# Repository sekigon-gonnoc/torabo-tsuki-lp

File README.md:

# torabo-tsuki LP

torabo-tsuki LP（トラボ付きLP）はトラックボール付きの無線分割キーボードキットです。

トラックボール(25 or 19mm)の高さを低く抑えることで、キーを打つときや持ち運びの邪魔になりにくくなっています。
無線接続に適したハードウェア・ソフトウェア構成により低消費電力を実現しており、連続して数か月間使用可能です。バッテリーは乾電池なので、残量や安全性を気にしながら定期的に充電する必要がありません。

[BOOTH](https://nogikes.booth.pm/items/7200248)にて販売中です。

**MX版の情報は[こちら](https://github.com/sekigon-gonnoc/torabo-tsuki)**

|||
|-|-|
|Sサイズ, 右25mmボール|Sサイズ, 右25mmボール|
|||
|Sサイズ, 右19mmボール|Sサイズ, 右19mmボール|

## [ビルドガイド](build-guide.md)

## 特徴

* 主要部品実装済み
  * ソケットやダイオードなどの部品は実装済みです。半田付けが必要な部品は電池ボックスだけです。
* 乾電池各1本で長期間動作
  * Ni-MH電池またはアルカリ電池で動作します。
  * 無線での使用にあわせて調整されたハードウェア・ソフトウェア構成により、乾電池でも数か月間利用できます。
* トラックボールの設置位置が調整可能
  * トラックボールを取り付ける位置を調整して、自分にとって一番操作しやすい位置に設置できます。ボールの高さを抑えたことでキーを打つときの邪魔になりにくなっています。
  * 左トラックボール、デュアルトラックボールにすることもできます。
  * トラックボールのサイズは25mmまたは19mmから選択できます。
* ZMK対応
  * keymap-editorやZMK Studioを使用して簡単にキーマップが変更できます。

## 使用上の注意

* 異臭や煙が出たときは、ただちに使用を中止して電源を切り電池を抜いてください。
* 電池から漏れた液が目に入った場合は、失明する恐れがあるのですぐにきれいな水でよく洗い、医師の診断を受けてください。
* 電池の+-を正しくセットしてください。
* 使い切った電池は速やかに取り出してください。
* 長期間使用しない場合は電池を取り出してください。

## 設計データについて

本リポジトリで基板・トラックボールケース・電池カバーの設計データを公開しています。

ライセンスにしたがって自由に利用していただいて構いませんが、問い合わせには対応しません。

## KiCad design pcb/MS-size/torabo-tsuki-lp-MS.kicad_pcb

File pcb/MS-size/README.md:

\# torabo-tsuki LP(MS)

Mサイズの17mmピッチ版です。

動作未確認

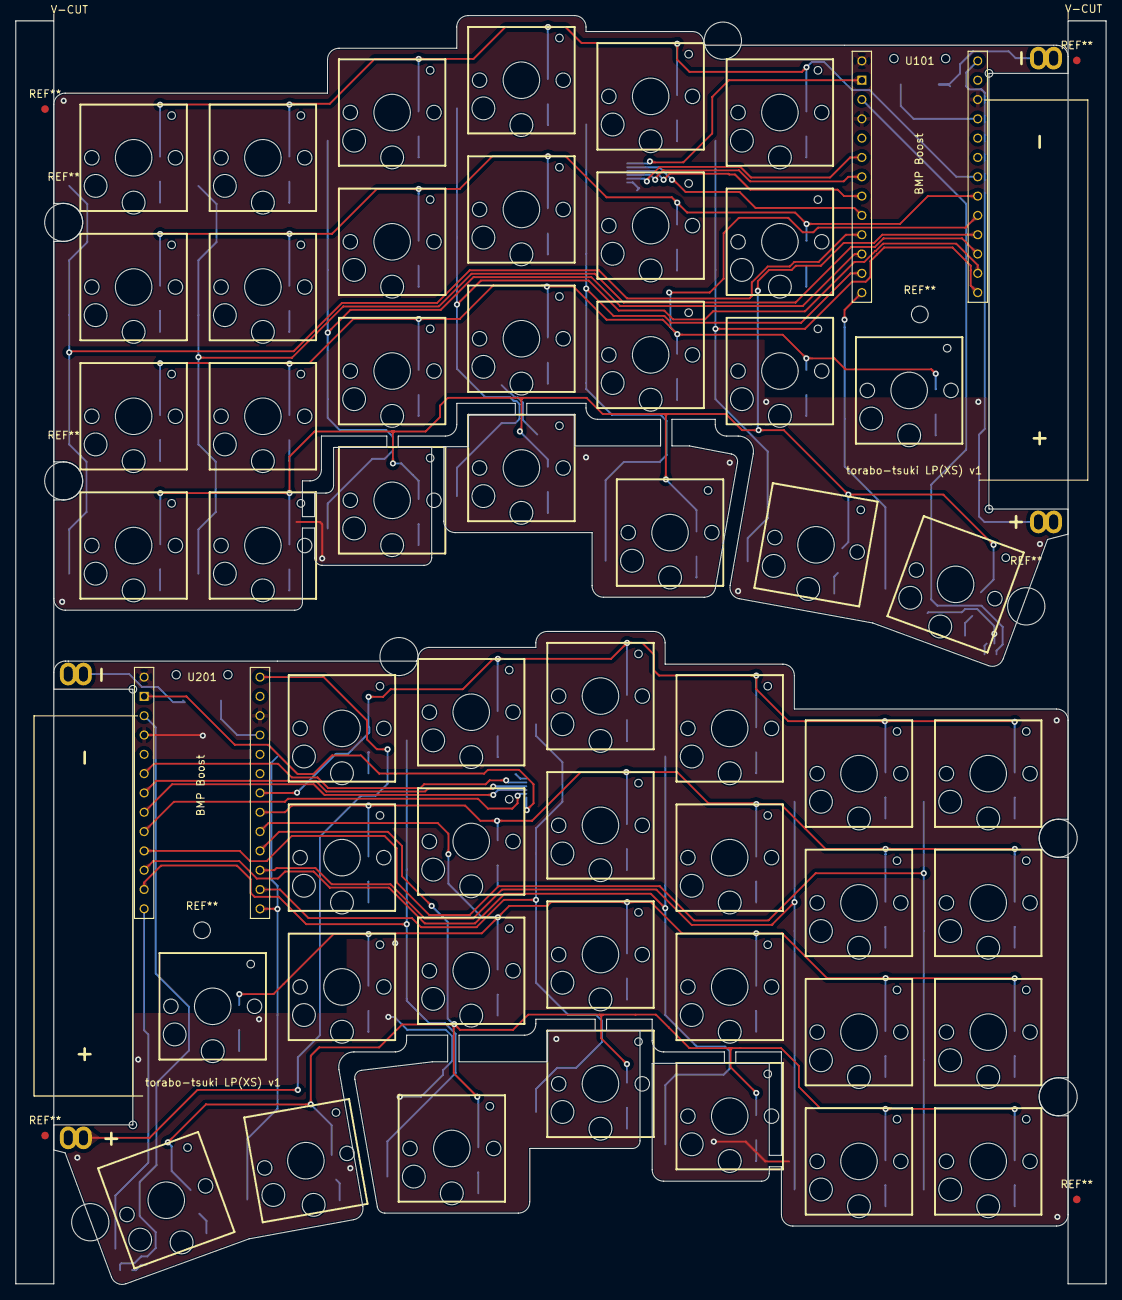
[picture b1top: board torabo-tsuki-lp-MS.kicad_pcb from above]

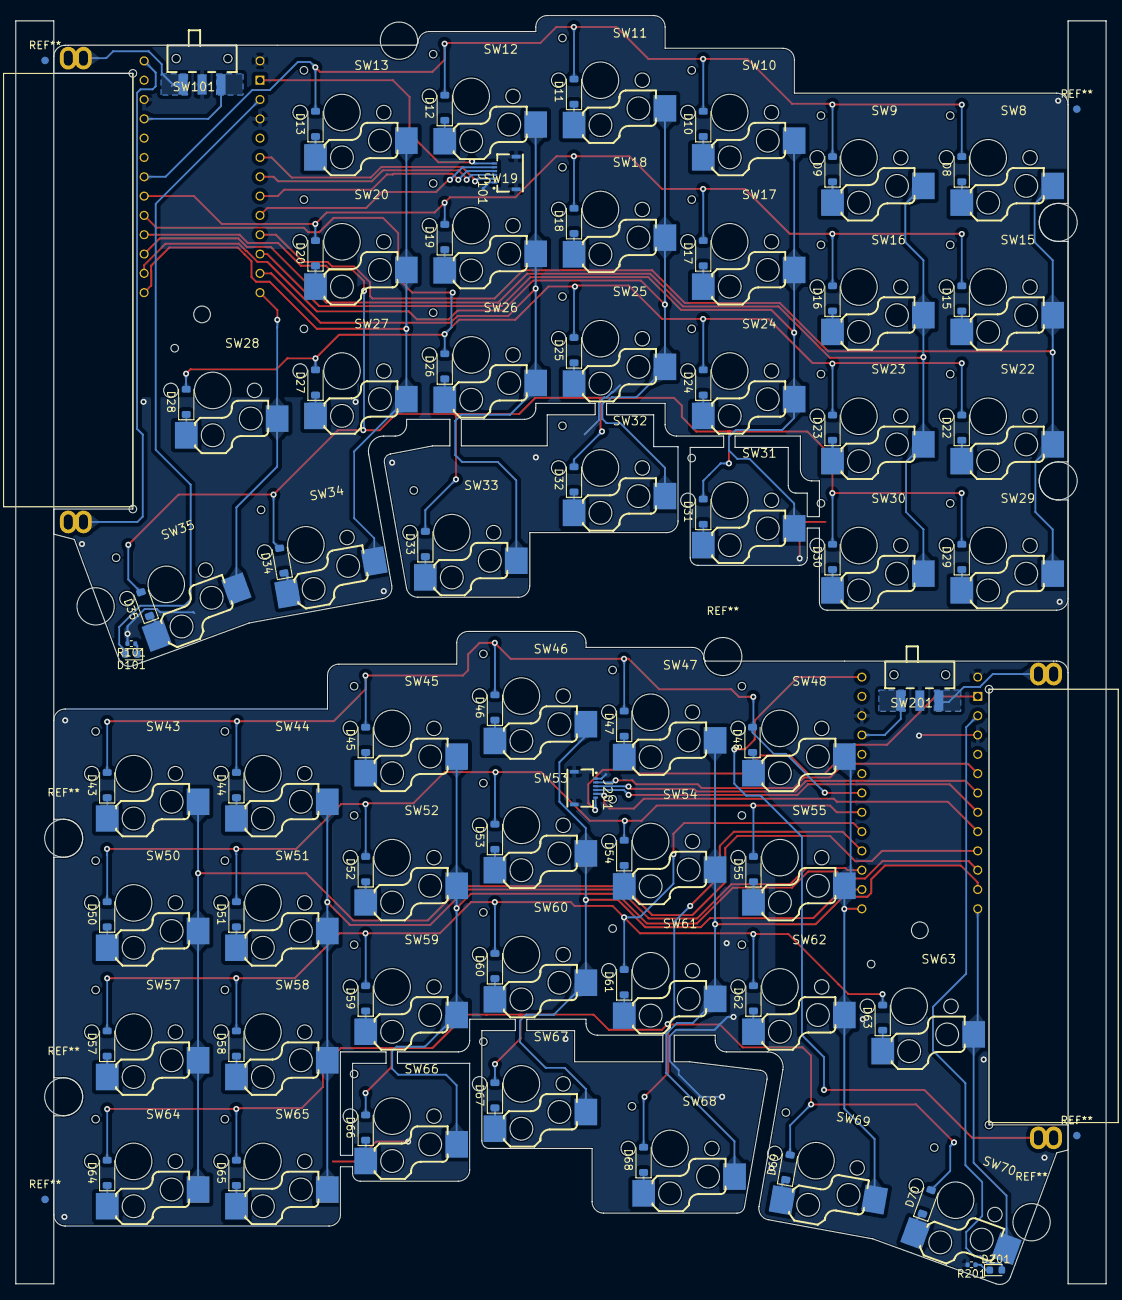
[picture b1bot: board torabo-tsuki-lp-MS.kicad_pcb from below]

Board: 2 copper layers, 143.4 x 166.8 mm, 118 parts (114 on the bottom side), 93 nets.

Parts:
BT101, BT201: Battery_Cell; battery_holder
BT102, BT202: Battery_Cell; AAA_Battery_DIP
D8, D9, D10, D11, D12, D13, D15, D16, D17, D18, D19, D20, D22, D23, D24, D25, D26, D27, D28, D29, D30, D31, D32, D33, D34, D35, D43, D44, D45, D46, D47, D48, D50, D51, D52, D53, D54, D55, D57, D58, D59, D60, D61, D62, D63, D64, D65, D66, D67, D68, D69, D70: D_Small; D_SOD-123
D101, D201: LED_Small; LED_0603_1608Metric
J101, J201: Conn_01x06_MountingPin; GT-F0501SR10-06S1101
R101, R201: 330; R_0402_1005Metric
SW8, SW9, SW10, SW11, SW12, SW13, SW15, SW16, SW17, SW18, SW19, SW20, SW22, SW23, SW24, SW25, SW26, SW27, SW28, SW29, SW30, SW31, SW32, SW33, SW34, SW35, SW43, SW44, SW45, SW46, SW47, SW48, SW50, SW51, SW52, SW53, SW54, SW55, SW57, SW58, SW59, SW60, SW61, SW62, SW63, SW64, SW65, SW66, SW67, SW68, SW69, SW70: SW_Push; CHOC_V2_SOCKET_HANDSOLDERING
SW101, SW201: SW_SPDT; SW-SMD_K3-1280S-F1
U101, U201: BLEMicroPro

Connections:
+BATT: BT101.1 (+), BT102.1 (+), BT201.1 (+), BT202.1 (+), U101.26 (BAT), U201.26 (BAT)
/left/BOOT: SW101.3 (C), U101.23 (BOOT)
/left/COL0: SW8.1, SW15.1, SW22.1, SW29.1, U101.10 (22)
/left/COL1: SW9.1, SW16.1, SW23.1, SW30.1, U101.16 (47)
/left/COL2: SW10.1, SW17.1, SW24.1, SW31.1, U101.11 (23)
/left/COL3: SW11.1, SW18.1, SW25.1, SW32.1, U101.15 (10)
/left/COL4: SW12.1, SW19.1, SW26.1, SW33.1, U101.12 (32)
/left/COL5: SW13.1, SW20.1, SW27.1, SW34.1, U101.14 (9)
/left/COL6: SW28.1, SW35.1, U101.13 (35)
/left/CS: J101.5, U101.9 (20)
/left/LED: D101.2 (A), U101.3 (11)
/left/MOTION: J101.4, U101.8 (19)
/left/ROW1: D8.2 (A), D9.2 (A), D10.2 (A), D11.2 (A), D12.2 (A), D13.2 (A), U101.20 (0)
/left/ROW2: D15.2 (A), D16.2 (A), D17.2 (A), D18.2 (A), D19.2 (A), D20.2 (A), U101.19 (30)
/left/ROW3: D22.2 (A), D23.2 (A), D24.2 (A), D25.2 (A), D26.2 (A), D27.2 (A), D28.2 (A), U101.18 (3)
/left/ROW4: D29.2 (A), D30.2 (A), D31.2 (A), D32.2 (A), D33.2 (A), D34.2 (A), D35.2 (A), U101.17 (46)
/left/SCLK: J101.2, U101.6 (18)
/left/SDIO: J101.3, U101.7 (16)
/right/BOOT: SW201.1 (A), U201.23 (BOOT)
/right/COL0: SW43.1, SW50.1, SW57.1, SW64.1, U201.10 (22)
/right/COL1: SW44.1, SW51.1, SW58.1, SW65.1, U201.16 (47)
/right/COL2: SW45.1, SW52.1, SW59.1, SW66.1, U201.11 (23)
/right/COL3: SW46.1, SW53.1, SW60.1, SW67.1, U201.15 (10)
/right/COL4: SW47.1, SW54.1, SW61.1, SW68.1, U201.12 (32)
/right/COL5: SW48.1, SW55.1, SW62.1, SW69.1, U201.14 (9)
/right/COL6: SW63.1, SW70.1, U201.13 (35)
/right/CS: J201.5, U201.9 (20)
/right/LED: D201.2 (A), U201.3 (11)
/right/MOTION: J201.4, U201.8 (19)
/right/ROW1: D43.2 (A), D44.2 (A), D45.2 (A), D46.2 (A), D47.2 (A), D48.2 (A), U201.20 (0)
/right/ROW2: D50.2 (A), D51.2 (A), D52.2 (A), D53.2 (A), D54.2 (A), D55.2 (A), U201.19 (30)
/right/ROW3: D57.2 (A), D58.2 (A), D59.2 (A), D60.2 (A), D61.2 (A), D62.2 (A), D63.2 (A), U201.18 (3)
/right/ROW4: D64.2 (A), D65.2 (A), D66.2 (A), D67.2 (A), D68.2 (A), D69.2 (A), D70.2 (A), U201.17 (46)
/right/SCLK: J201.2, U201.6 (18)
/right/SDIO: J201.3, U201.7 (16)
GND: J101.1, J101.MP (MountPin), J201.1, J201.MP (MountPin), R101.2, R201.2, SW101.2 (B), SW201.2 (B), U101.1 (GND), U101.4 (GND), U101.24 (GND), U201.1 (GND), U201.4 (GND), U201.24 (GND)
unnamed: BT101.2 (-), BT102.2 (-), SW101.1 (A)
unnamed: BT201.2 (-), BT202.2 (-), SW201.3 (C)
unnamed: D8.1 (K), SW8.2
unnamed: D9.1 (K), SW9.2
unnamed: D10.1 (K), SW10.2
unnamed: D11.1 (K), SW11.2
unnamed: D12.1 (K), SW12.2
unnamed: D13.1 (K), SW13.2
unnamed: D15.1 (K), SW15.2
unnamed: D16.1 (K), SW16.2
unnamed: D17.1 (K), SW17.2
unnamed: D18.1 (K), SW18.2
unnamed: D19.1 (K), SW19.2
unnamed: D20.1 (K), SW20.2
unnamed: D22.1 (K), SW22.2
unnamed: D23.1 (K), SW23.2
unnamed: D24.1 (K), SW24.2
unnamed: D25.1 (K), SW25.2
unnamed: D26.1 (K), SW26.2
unnamed: D27.1 (K), SW27.2
unnamed: D28.1 (K), SW28.2
unnamed: D29.1 (K), SW29.2
unnamed: D30.1 (K), SW30.2
unnamed: D31.1 (K), SW31.2
unnamed: D32.1 (K), SW32.2
unnamed: D33.1 (K), SW33.2
unnamed: D34.1 (K), SW34.2
unnamed: D35.1 (K), SW35.2
unnamed: D43.1 (K), SW43.2
unnamed: D44.1 (K), SW44.2
unnamed: D45.1 (K), SW45.2
unnamed: D46.1 (K), SW46.2
unnamed: D47.1 (K), SW47.2
unnamed: D48.1 (K), SW48.2
unnamed: D50.1 (K), SW50.2
unnamed: D51.1 (K), SW51.2
unnamed: D52.1 (K), SW52.2
unnamed: D53.1 (K), SW53.2
unnamed: D54.1 (K), SW54.2
unnamed: D55.1 (K), SW55.2
unnamed: D57.1 (K), SW57.2
unnamed: D58.1 (K), SW58.2
unnamed: D59.1 (K), SW59.2
unnamed: D60.1 (K), SW60.2
unnamed: D61.1 (K), SW61.2
unnamed: D62.1 (K), SW62.2
unnamed: D63.1 (K), SW63.2
unnamed: D64.1 (K), SW64.2
unnamed: D65.1 (K), SW65.2
unnamed: D66.1 (K), SW66.2
unnamed: D67.1 (K), SW67.2
unnamed: D68.1 (K), SW68.2
unnamed: D69.1 (K), SW69.2
unnamed: D70.1 (K), SW70.2
unnamed: D101.1 (K), R101.1
unnamed: D201.1 (K), R201.1
VCC: J101.6, J201.6, U101.2 (8), U201.2 (8)

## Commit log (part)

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2025-07-19 Update image
2026-06-15 feat: add L version PCB design files
2026-06-17 Add XS(v1) plate date
2026-06-22 Add XS, L size pcb data
2026-06-28 Add MS-size
